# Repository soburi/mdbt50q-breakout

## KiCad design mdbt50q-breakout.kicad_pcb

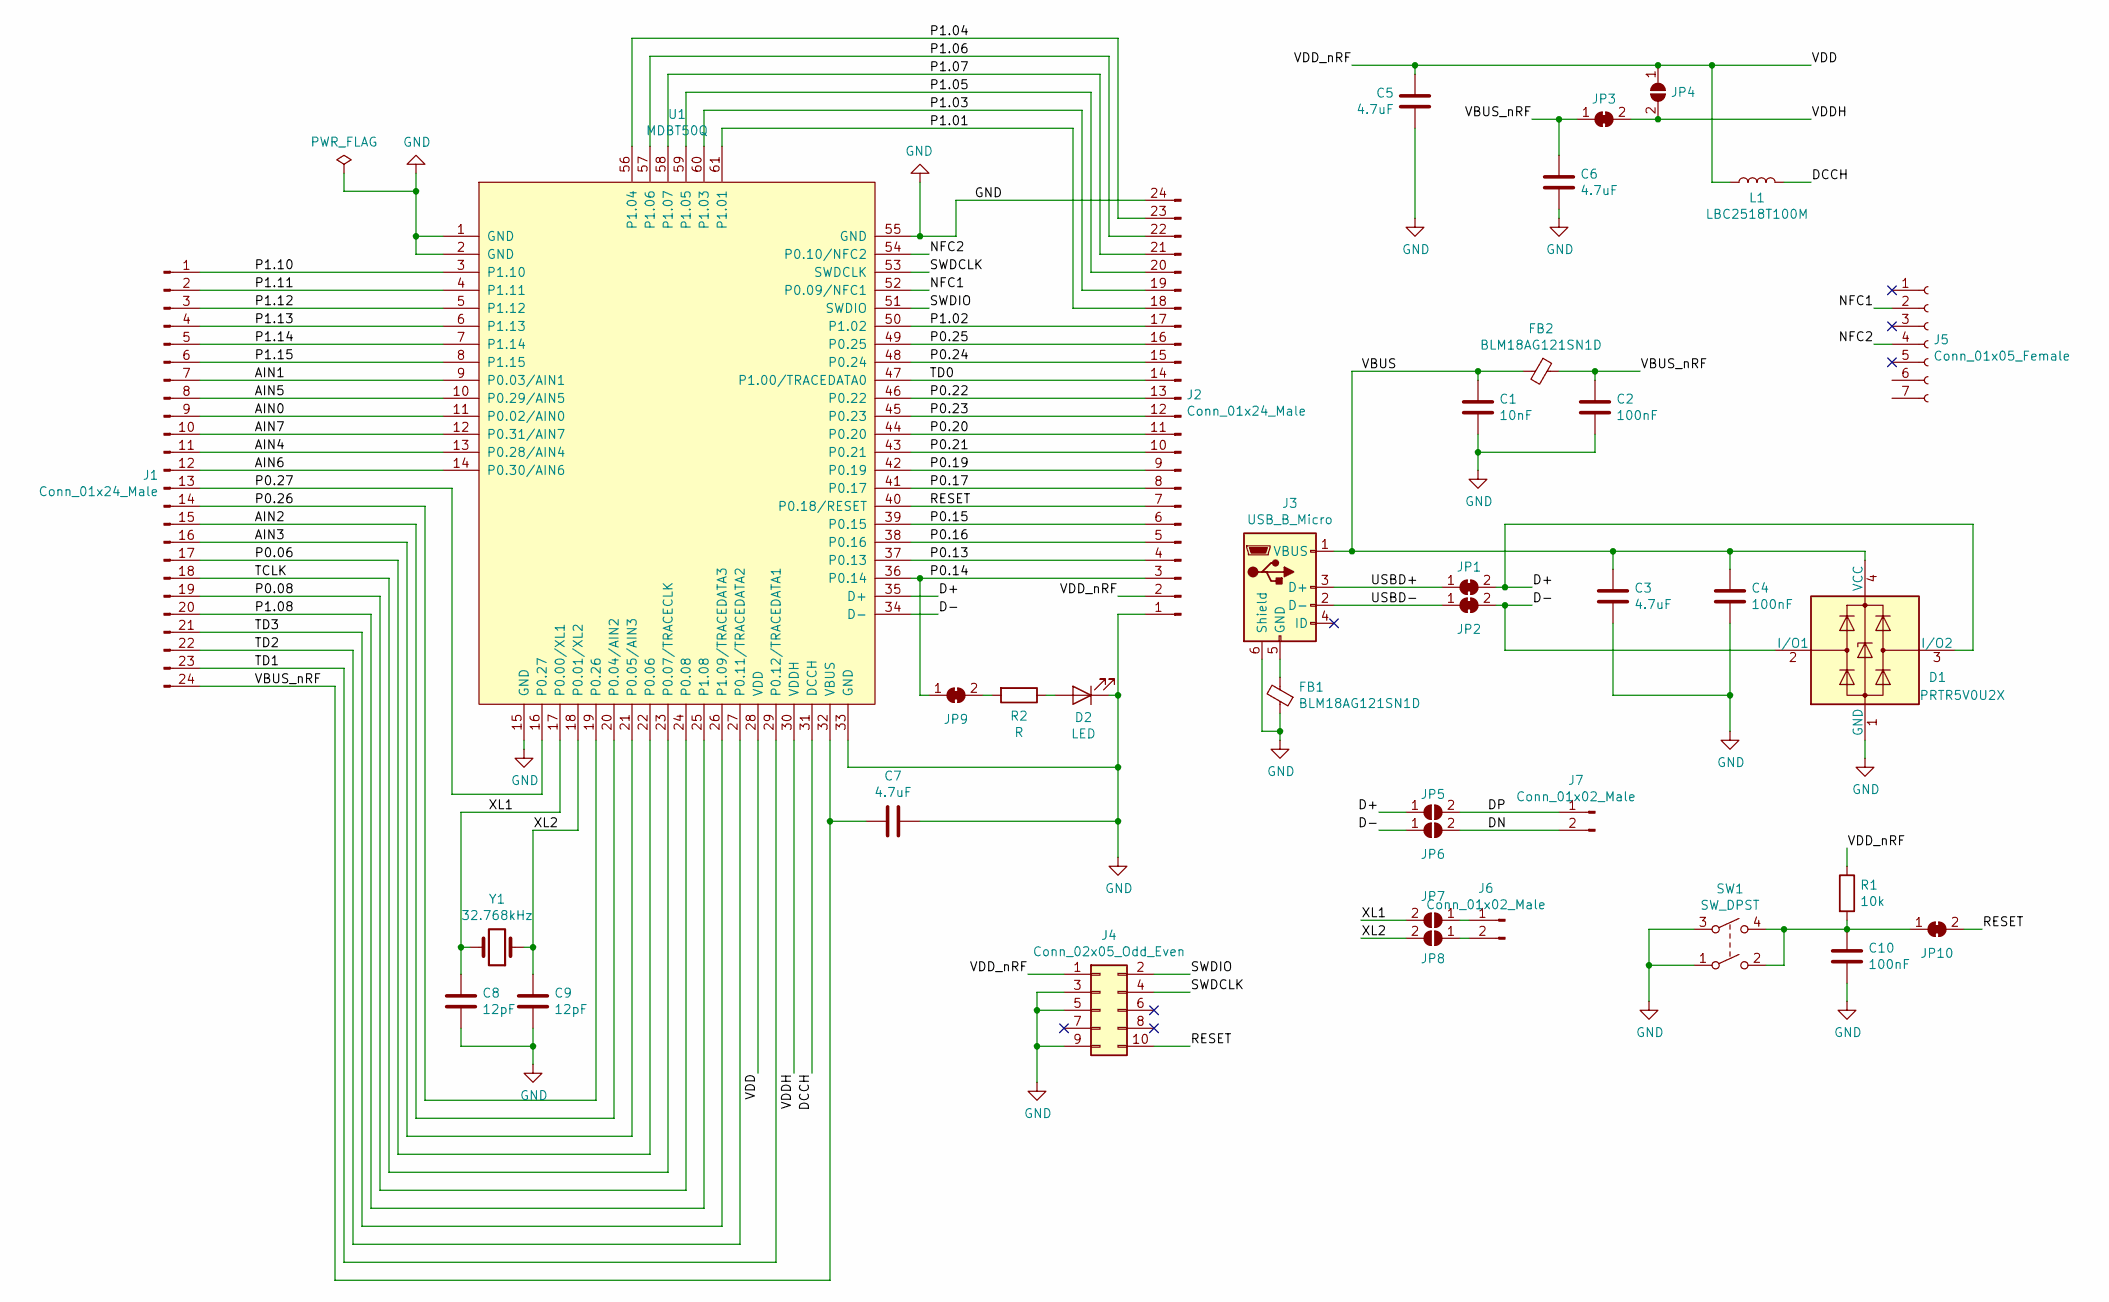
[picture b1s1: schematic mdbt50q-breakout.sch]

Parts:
C1: 10nF; C_0603_1608Metric
C2, C4, C10: 100nF; C_0603_1608Metric
C3, C5, C6, C7: 4.7uF; C_0603_1608Metric
C8, C9: 12pF; C_0603_1608Metric
D1: PRTR5V0U2X; SOT-143
D2: LED; LED_0805_2012Metric
FB1, FB2: BLM18AG121SN1D; L_0603_1608Metric
J1, J2: Conn_01x24_Male; PinHeader_1x24_P2.54mm_Vertical
J3: USB_B_Micro; zx62-b-5pa
J4: Conn_02x05_Odd_Even; PinHeader_2x05_P1.27mm_Vertical_SMD
J5: Conn_01x05_Female; 0512810594
J6, J7: Conn_01x02_Male; PinHeader_1x02_P2.54mm_Vertical
JP1, JP2, JP3, JP9, JP10: SolderJumper_2_Bridged; SolderJumper-2_P1.3mm_Bridged_RoundedPad1.0x1.5mm
JP4, JP5, JP6, JP7, JP8: SolderJumper_2_Open; SolderJumper-2_P1.3mm_Open_RoundedPad1.0x1.5mm
L1: LBC2518T100M; L_taiyo_yuden_2518Metric
R1: 10k; R_0603_1608Metric
R2: R; R_0603_1608Metric
SW1: SW_DPST; SKRPACE010
U1: MDBT50Q
Y1: 32.768kHz; Crystal_SMD_3215-2Pin_3.2x1.5mm

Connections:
/AIN0: J1.9, U1.11 (P0.02/AIN0)
/AIN1: J1.7, U1.9 (P0.03/AIN1)
/AIN2: J1.15, U1.20 (P0.04/AIN2)
/AIN3: J1.16, U1.21 (P0.05/AIN3)
/AIN4: J1.11, U1.13 (P0.28/AIN4)
/AIN5: J1.8, U1.10 (P0.29/AIN5)
/AIN6: J1.12, U1.14 (P0.30/AIN6)
/AIN7: J1.10, U1.12 (P0.31/AIN7)
/D+: D1.3 (I/O2), JP1.2 (B), JP5.1 (A), U1.35 (D+)
/D-: D1.2 (I/O1), JP2.2 (B), JP6.1 (A), U1.34 (D-)
/DCCH: L1.2, U1.31 (DCCH)
/DN: J7.2, JP6.2 (B)
/DP: J7.1, JP5.2 (B)
/NFC1: J5.2, U1.52 (P0.09/NFC1)
/NFC2: J5.4, U1.54 (P0.10/NFC2)
/P0.06: J1.17, U1.22 (P0.06)
/P0.08: J1.19, U1.24 (P0.08)
/P0.13: J2.4, U1.37 (P0.13)
/P0.14: J2.3, JP9.1 (A), U1.36 (P0.14)
/P0.15: J2.6, U1.39 (P0.15)
/P0.16: J2.5, U1.38 (P0.16)
/P0.17: J2.8, U1.41 (P0.17)
/P0.19: J2.9, U1.42 (P0.19)
/P0.20: J2.11, U1.44 (P0.20)
/P0.21: J2.10, U1.43 (P0.21)
/P0.22: J2.13, U1.46 (P0.22)
/P0.23: J2.12, U1.45 (P0.23)
/P0.24: J2.15, U1.48 (P0.24)
/P0.25: J2.16, U1.49 (P0.25)
/P0.26: J1.14, U1.19 (P0.26)
/P0.27: J1.13, U1.16 (P0.27)
/P1.01: J2.18, U1.61 (P1.01)
/P1.02: J2.17, U1.50 (P1.02)
/P1.03: J2.19, U1.60 (P1.03)
/P1.04: J2.23, U1.56 (P1.04)
/P1.05: J2.20, U1.59 (P1.05)
/P1.06: J2.22, U1.57 (P1.06)
/P1.07: J2.21, U1.58 (P1.07)
/P1.08: J1.20, U1.25 (P1.08)
/P1.10: J1.1, U1.3 (P1.10)
/P1.11: J1.2, U1.4 (P1.11)
/P1.12: J1.3, U1.5 (P1.12)
/P1.13: J1.4, U1.6 (P1.13)
/P1.14: J1.5, U1.7 (P1.14)
/P1.15: J1.6, U1.8 (P1.15)
/RESET: J2.7, J4.10, JP10.2 (B), U1.40 (P0.18/RESET)
/SWDCLK: J4.4, U1.53 (SWDCLK)
/SWDIO: J4.2, U1.51 (SWDIO)
/TCLK: J1.18, U1.23 (P0.07/TRACECLK)
/TD0: J2.14, U1.47 (P1.00/TRACEDATA0)
/TD1: J1.23, U1.29 (P0.12/TRACEDATA1)
/TD2: J1.22, U1.27 (P0.11/TRACEDATA2)
/TD3: J1.21, U1.26 (P1.09/TRACEDATA3)
/USBD+: J3.3 (D+), JP1.1 (A)
/USBD-: J3.2 (D-), JP2.1 (A)
/VBUS: C1.1, C3.1, C4.1, D1.4 (VCC), FB2.2, J3.1 (VBUS)
/VBUS_nRF: C2.1, C6.1, C7.1, FB2.1, J1.24, JP3.1 (A), U1.32 (VBUS)
/VDD: C5.1, J2.2, J4.1, JP4.1 (A), L1.1, R1.1, U1.28 (VDD)
/VDDH: JP3.2 (B), JP4.2 (B), U1.30 (VDDH)
/XL1: C8.1, JP7.2 (B), U1.17 (P0.00/XL1), Y1.2
/XL2: C9.1, JP8.2 (B), U1.18 (P0.01/XL2), Y1.1
GND: C1.2, C2.2, C3.2, C4.2, C5.2, C6.2, C7.2, C8.2, C9.2, C10.2, D1.1 (GND), D2.1 (K), FB1.1, J2.1, J2.24, J3.6 (Shield), J4.3, J4.5, J4.9, SW1.1, SW1.3, U1.1 (GND), U1.2 (GND), U1.15 (GND), U1.33 (GND), U1.55 (GND)
unnamed: C10.1, JP10.1 (A), R1.2, SW1.2, SW1.4
unnamed: D2.2 (A), R2.1
unnamed: FB1.2, J3.5 (GND)
unnamed: J6.1, JP7.1 (A)
unnamed: J6.2, JP8.1 (A)
unnamed: JP9.2 (B), R2.2

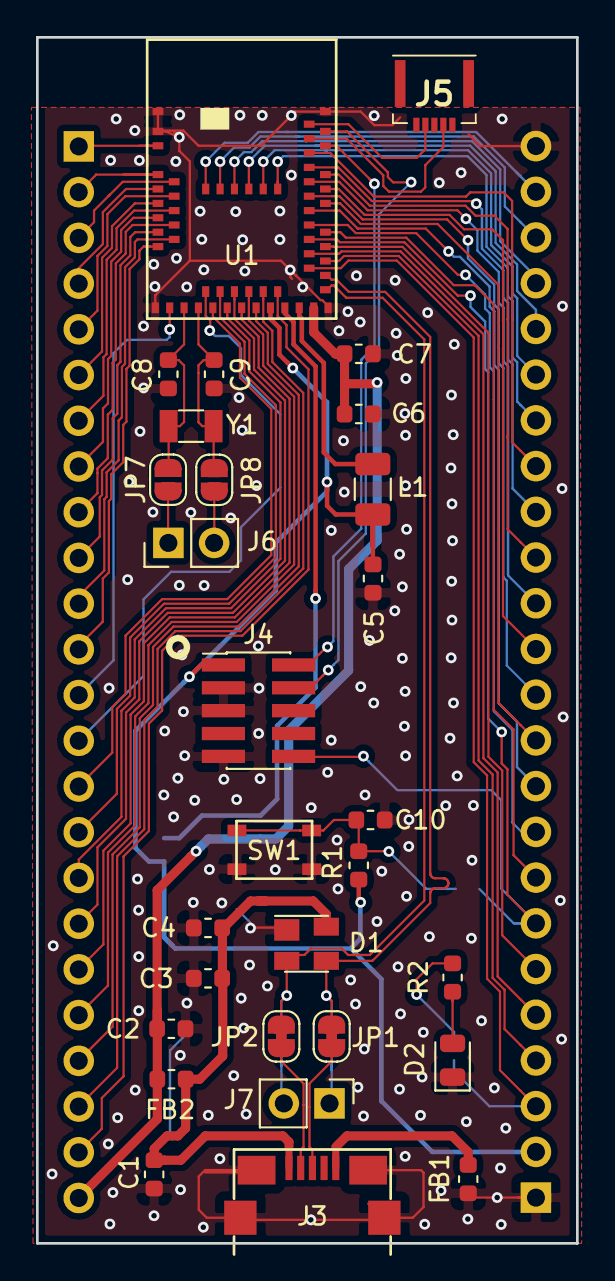
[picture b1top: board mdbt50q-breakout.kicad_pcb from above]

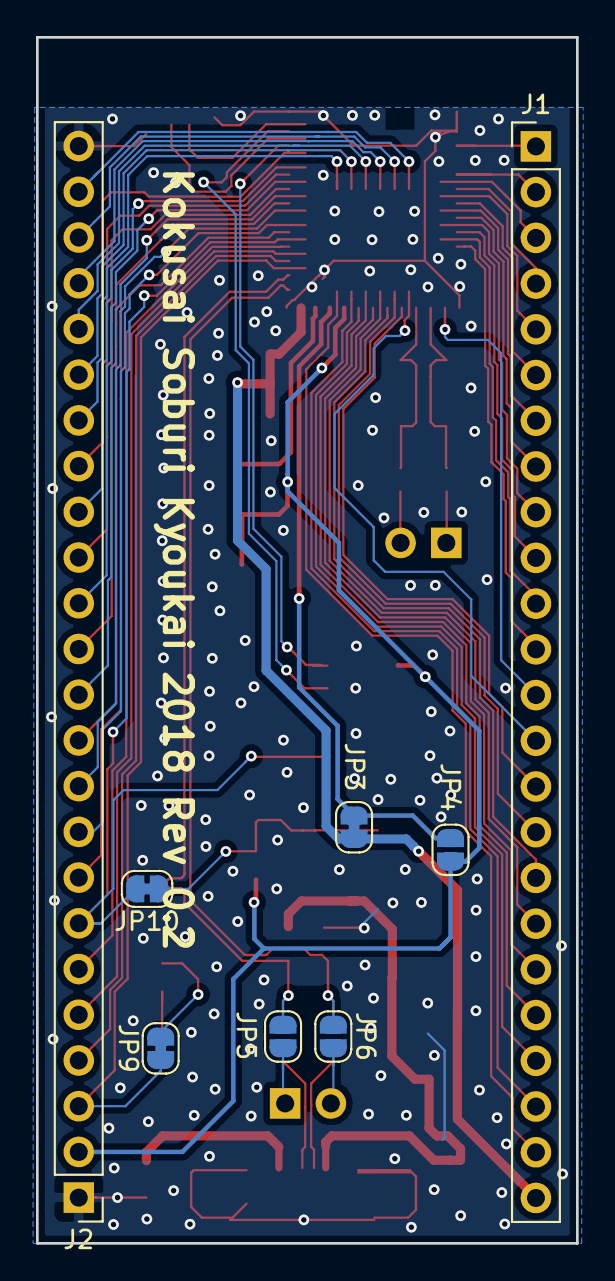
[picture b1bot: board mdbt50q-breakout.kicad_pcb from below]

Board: 2 copper layers, 30.0 x 67.0 mm, 37 parts (8 on the bottom side), 68 nets.

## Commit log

2018-12-29 initial
